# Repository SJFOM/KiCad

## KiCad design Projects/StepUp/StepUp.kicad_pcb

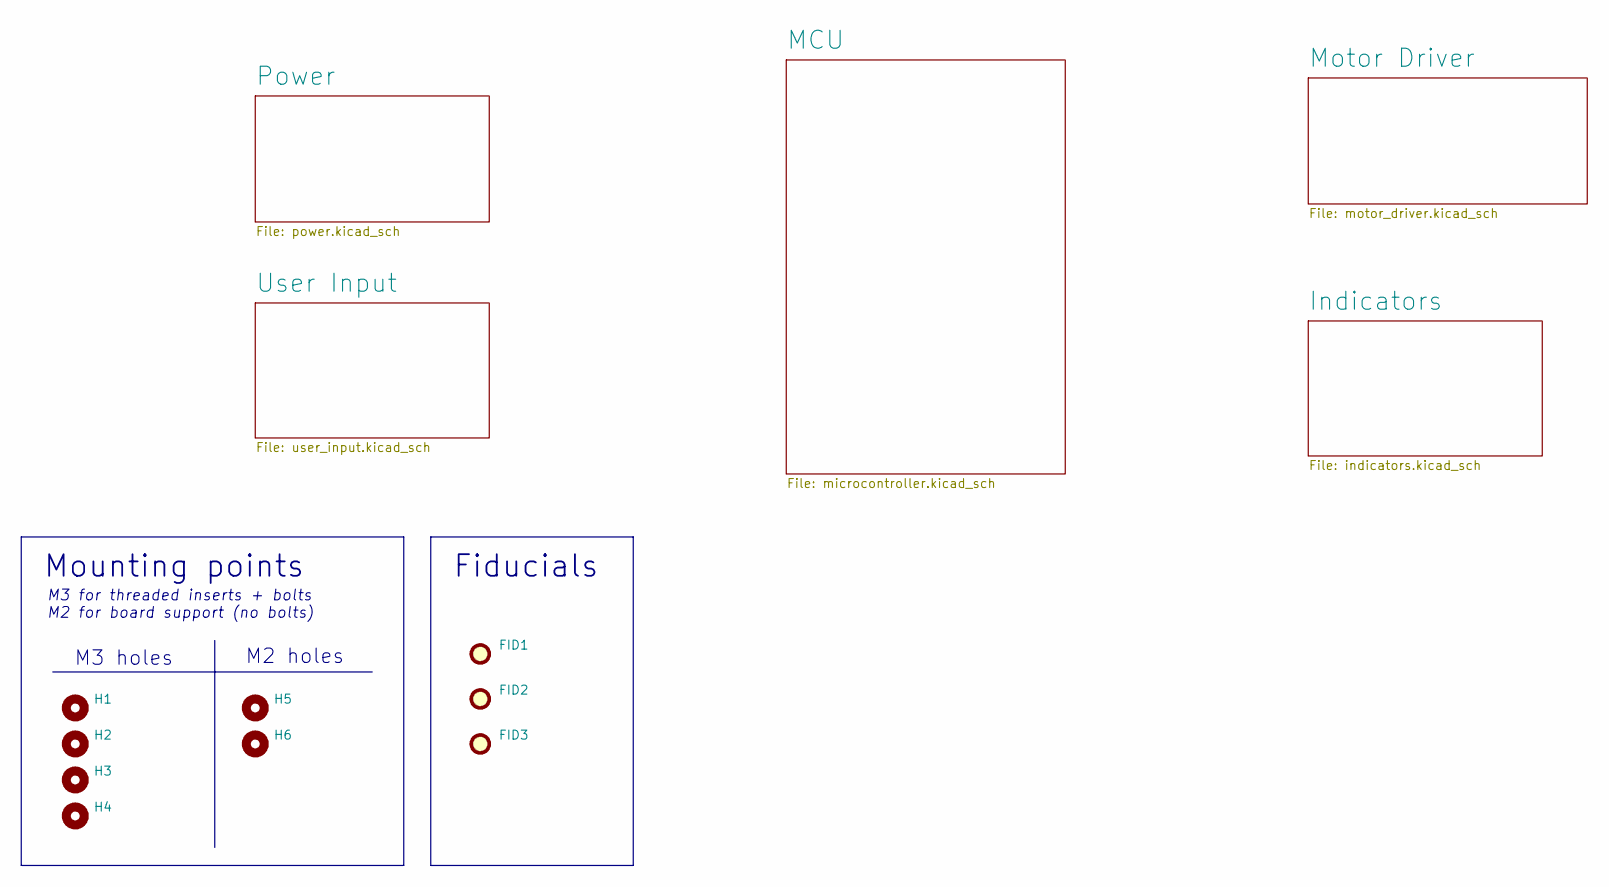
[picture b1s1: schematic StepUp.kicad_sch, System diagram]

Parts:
FID1, FID2, FID3: Fiducial; Fiducial_1mm_Mask2mm
H1, H2, H3, H4: MountingHole; MountingHole_3.2mm_M3_DIN965
H5, H6: MountingHole; MountingHole_2.2mm_M2

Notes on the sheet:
Mounting points
M3 holes
M2 holes
Fiducials
M3 for threaded inserts + bolts M2 for board support (no bolts)

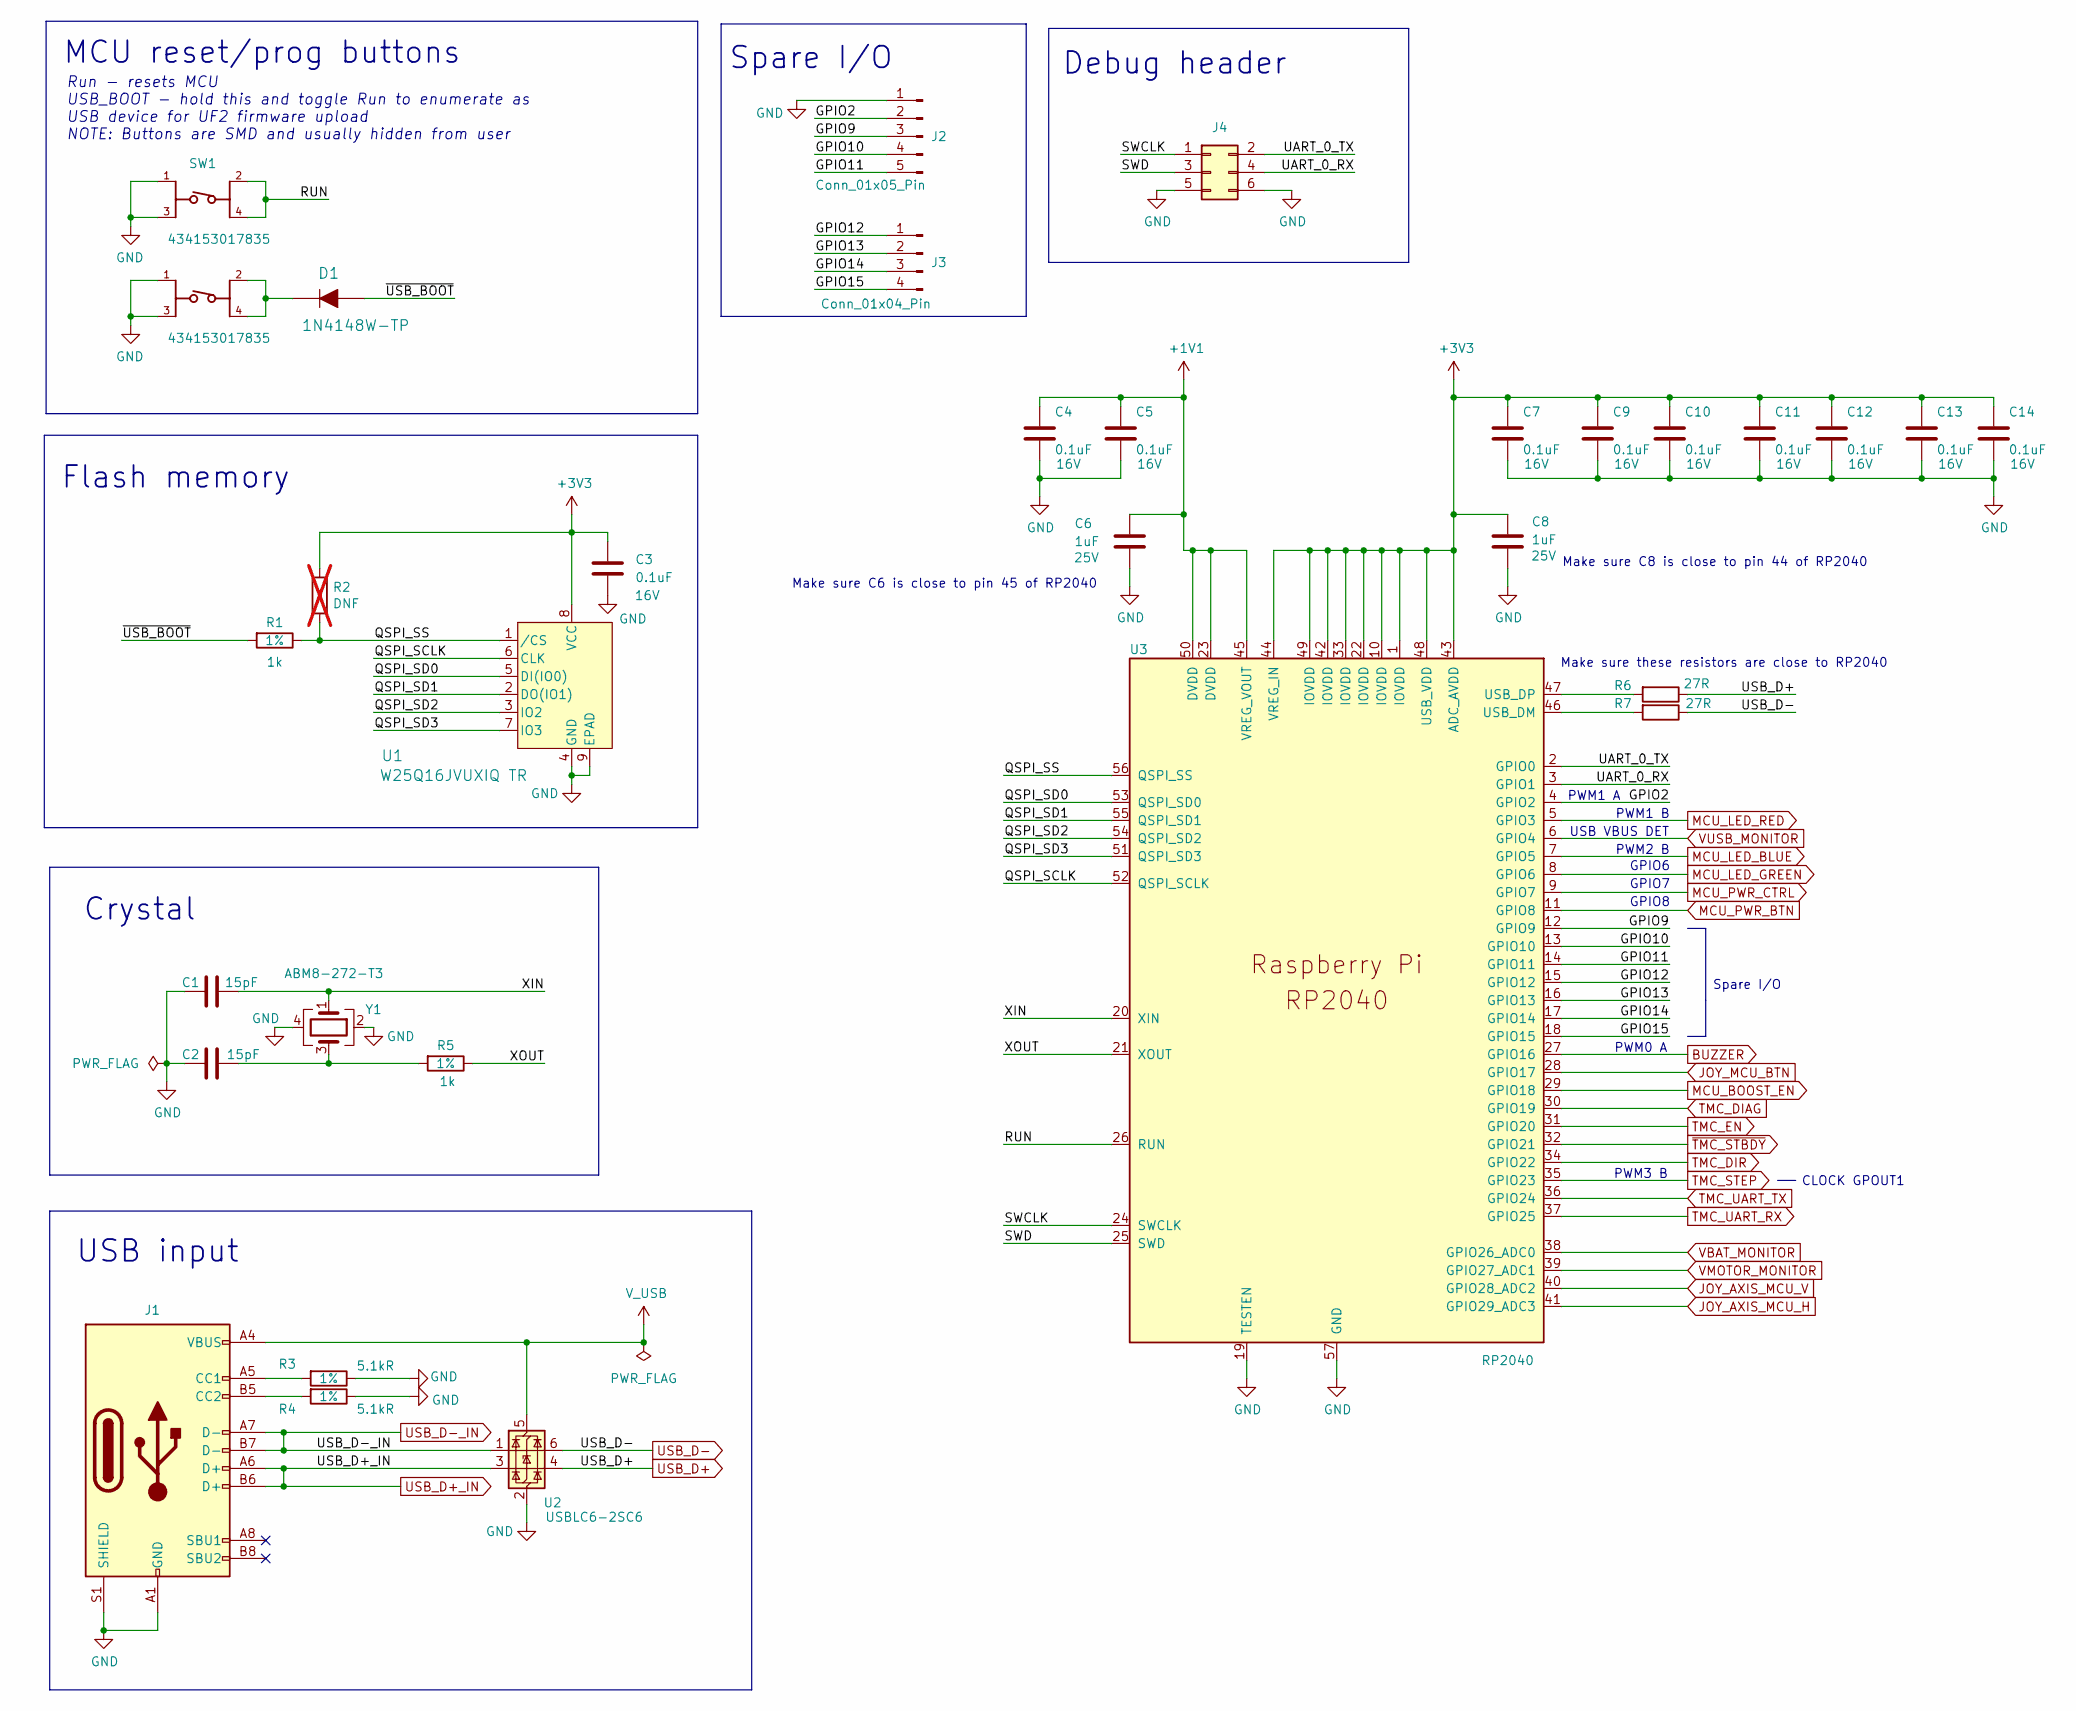
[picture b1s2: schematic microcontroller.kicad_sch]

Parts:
C1, C2: 15pF; C_0402_1005Metric; Tolerance 1%; Voltage 50V; MPN CC0402FRNPO9BN150
C3, C4, C5, C7, C9, C10, C11, C12, C13, C14: 0.1uF; C_0402_1005Metric; Voltage 16V; Tolerance 10%; MPN GRM155R61C104KA88D
C6, C8: 1uF; C_0603_1608Metric; Voltage 25V; Tolerance 10%; MPN GRM188R71E105KA12D
D1: 1N4148W-TP; SOD-123; MPN 1N4148W-TP; Digi-Key_PN 1N4148WTPMSCT-ND
J1: USB_C_Receptacle_USB2.0_16P; USB_C_Receptacle_GCT_USB4105-xx-A_16P_TopMnt_Horizontal; MPN USB4105-GF-A
J2: Conn_01x05_Pin; PinHeader_1x05_P2.54mm_Vertical
J3: Conn_01x04_Pin; PinHeader_1x04_P2.54mm_Vertical
J4: Conn_02x03_Odd_Even; PinHeader_2x03_P2.54mm_Vertical
R1, R5: 1k; R_0402_1005Metric; Tolerance 1%; MPN RC0402FR-071KL
R2: DNF; R_0402_1005Metric; not fitted
R3, R4: 5.1kR; R_0603_1608Metric; Tolerance 1%; MPN RC0603FR-075K1L
R6, R7: 27R; R_0402_1005Metric; Tolerance 1%; MPN RC0402FR-0727RL
SW1, SW2: 434153017835; 434153017835_434153017835; Voltage 12VDC; PART-NUMBER 434153017835
U1: W25Q16JVUXIQ TR; USON-8_UX_2x3x0p6_WIN; MPN W25Q16JVUXIQ TR
U2: USBLC6-2SC6; SOT-23-6; MPN USBLC6-2SC6
U3: RP2040; RP2040-QFN-56; MPN RP2040
Y1: ABM8-272-T3; Crystal_SMD_3225-4Pin_3.2x2.5mm; MPN ABM8-272-T3

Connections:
+1V1: C4.1, C5.1, C6.1, U3.23 (DVDD), U3.45 (VREG_VOUT), U3.50 (DVDD)
+3V3: C3.1, C7.1, C8.1, C9.1, C10.1, C11.1, C12.1, C13.1, C14.1, R2.1, U1.8 (VCC), U3.1 (IOVDD), U3.10 (IOVDD), U3.22 (IOVDD), U3.33 (IOVDD), U3.42 (IOVDD), U3.43 (ADC_AVDD), U3.44 (VREG_IN), U3.48 (USB_VDD), U3.49 (IOVDD); also elsewhere on the board
/MCU/GPIO2: J2.2, U3.4 (GPIO2)
/MCU/GPIO9: J2.3, U3.12 (GPIO9)
/MCU/GPIO10: J2.4, U3.13 (GPIO10)
/MCU/GPIO11: J2.5, U3.14 (GPIO11)
/MCU/GPIO12: J3.1, U3.15 (GPIO12)
/MCU/GPIO13: J3.2, U3.16 (GPIO13)
/MCU/GPIO14: J3.3, U3.17 (GPIO14)
/MCU/GPIO15: J3.4, U3.18 (GPIO15)
/MCU/QSPI_SCLK: U1.6 (CLK), U3.52 (QSPI_SCLK)
/MCU/QSPI_SD0: U1.5 (DI(IO0)), U3.53 (QSPI_SD0)
/MCU/QSPI_SD1: U1.2 (DO(IO1)), U3.55 (QSPI_SD1)
/MCU/QSPI_SD2: U1.3 (IO2), U3.54 (QSPI_SD2)
/MCU/QSPI_SD3: U1.7 (IO3), U3.51 (QSPI_SD3)
/MCU/QSPI_SS: R1.1, R2.2, U1.1 (/CS), U3.56 (QSPI_SS)
/MCU/RUN: SW1.2, SW1.4, U3.26 (RUN)
/MCU/SWCLK: J4.1, U3.24 (SWCLK)
/MCU/SWD: J4.3, U3.25 (SWD)
/MCU/UART_0_RX: J4.4, U3.3 (GPIO1)
/MCU/UART_0_TX: J4.2, U3.2 (GPIO0)
/MCU/XIN: C1.1, U3.20 (XIN), Y1.1
/MCU/XOUT: R5.1, U3.21 (XOUT)
/MCU/~USB_BOOT: D1.A, R1.2
BUZZER: U3.27 (GPIO16); also elsewhere on the board
GND: C1.2, C2.2, C3.2, C4.2, C5.2, C6.2, C7.2, C8.2, C9.2, C10.2, C11.2, C12.2, C13.2, C14.2, J1.A1 (GND), J1.A12 (GND), J1.B1 (GND), J1.B12 (GND), J1.S1 (SHIELD), J2.1, J4.5, J4.6, R3.1, R4.1, SW1.1, SW1.3, SW2.1, SW2.3, U1.4 (GND), U1.9 (EPAD), U2.2 (GND), U3.19 (TESTEN), U3.57 (GND), Y1.2, Y1.4; also elsewhere on the board
JOY_AXIS_MCU_H: U3.41 (GPIO29_ADC3); also elsewhere on the board
JOY_AXIS_MCU_V: U3.40 (GPIO28_ADC2); also elsewhere on the board
JOY_MCU_BTN: U3.28 (GPIO17); also elsewhere on the board
MCU_BOOST_EN: U3.29 (GPIO18); also elsewhere on the board
MCU_LED_BLUE: U3.7 (GPIO5); also elsewhere on the board
MCU_LED_GREEN: U3.8 (GPIO6); also elsewhere on the board
MCU_LED_RED: U3.5 (GPIO3); also elsewhere on the board
MCU_PWR_BTN: U3.11 (GPIO8); also elsewhere on the board
MCU_PWR_CTRL: U3.9 (GPIO7); also elsewhere on the board
unnamed: C2.1, R5.2, Y1.3
unnamed: D1.K, SW2.2, SW2.4
unnamed: J1.A5 (CC1), R3.2
unnamed: J1.B5 (CC2), R4.2
unnamed: R7.2, U3.46 (USB_DM)
unnamed: R6.2, U3.47 (USB_DP)
TMC_DIAG: U3.30 (GPIO19); also elsewhere on the board
TMC_DIR: U3.34 (GPIO22); also elsewhere on the board
TMC_EN: U3.31 (GPIO20); also elsewhere on the board
TMC_STEP: U3.35 (GPIO23); also elsewhere on the board
TMC_UART_RX: U3.37 (GPIO25); also elsewhere on the board
TMC_UART_TX: U3.36 (GPIO24); also elsewhere on the board
USB_D+: R6.1, U2.4 (I/O2)
USB_D+_IN: J1.A6 (D+), J1.B6 (D+), U2.3 (I/O2)
USB_D-: R7.1, U2.6 (I/O1)
USB_D-_IN: J1.A7 (D-), J1.B7 (D-), U2.1 (I/O1)
VBAT_MONITOR: U3.38 (GPIO26_ADC0); also elsewhere on the board
VMOTOR_MONITOR: U3.39 (GPIO27_ADC1); also elsewhere on the board
VUSB_MONITOR: U3.6 (GPIO4); also elsewhere on the board
V_USB: J1.A4 (VBUS), J1.A9 (VBUS), J1.B4 (VBUS), J1.B9 (VBUS), U2.5 (VBUS); also elsewhere on the board
~TMC_STBDY: U3.32 (GPIO21); also elsewhere on the board

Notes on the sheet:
CLOCK GPOUT1
GPIO6
Spare I/O
Make sure C8 is close to pin 44 of RP2040
Make sure C6 is close to pin 45 of RP2040
Debug header
PWM0 A
USB VBUS DET
MCU reset/prog buttons
Flash memory
PWM1 A
Crystal
PWM3 B
USB input
GPIO7
Run - resets MCU USB_BOOT - hold this and toggle Run to enumerate as USB device for UF2 firmware upload NOTE: Buttons are SMD and usually hidden from user
PWM2 B
PWM1 B
GPIO8
Make sure these resistors are close to RP2040

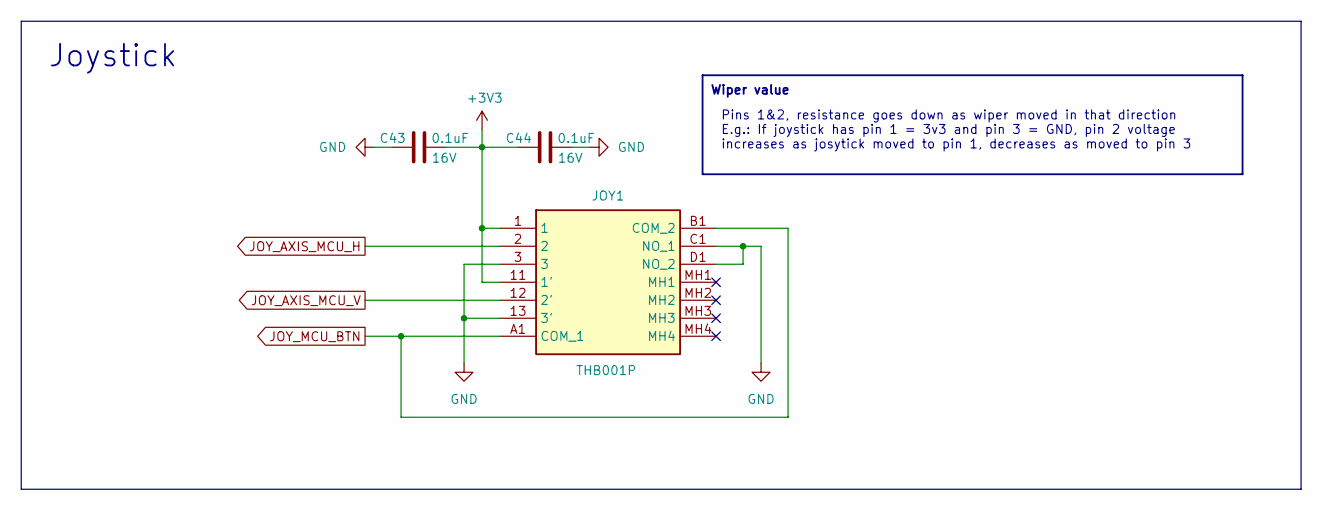
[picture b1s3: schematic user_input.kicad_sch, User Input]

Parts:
C43, C44: 0.1uF; C_0402_1005Metric; Voltage 16V; Tolerance 10%; MPN GRM155R61C104KA88D
JOY1: THB001P; Mouser Part Number 611-THB001P

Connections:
+3V3: C43.2, C44.1, JOY1.1, JOY1.11 (1'); also elsewhere on the board
GND: C43.1, C44.2, JOY1.3, JOY1.13 (3'), JOY1.C1 (NO_1), JOY1.D1 (NO_2); also elsewhere on the board
JOY_AXIS_MCU_H: JOY1.2; also elsewhere on the board
JOY_AXIS_MCU_V: JOY1.12 (2'); also elsewhere on the board
JOY_MCU_BTN: JOY1.A1 (COM_1), JOY1.B1 (COM_2); also elsewhere on the board

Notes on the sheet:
Wiper value
Pins 1&2, resistance goes down as wiper moved in that direction E.g.: If joystick has pin 1 = 3v3 and pin 3 = GND, pin 2 voltage increases as josytick moved to pin 1, decreases as moved to pin 3
Joystick

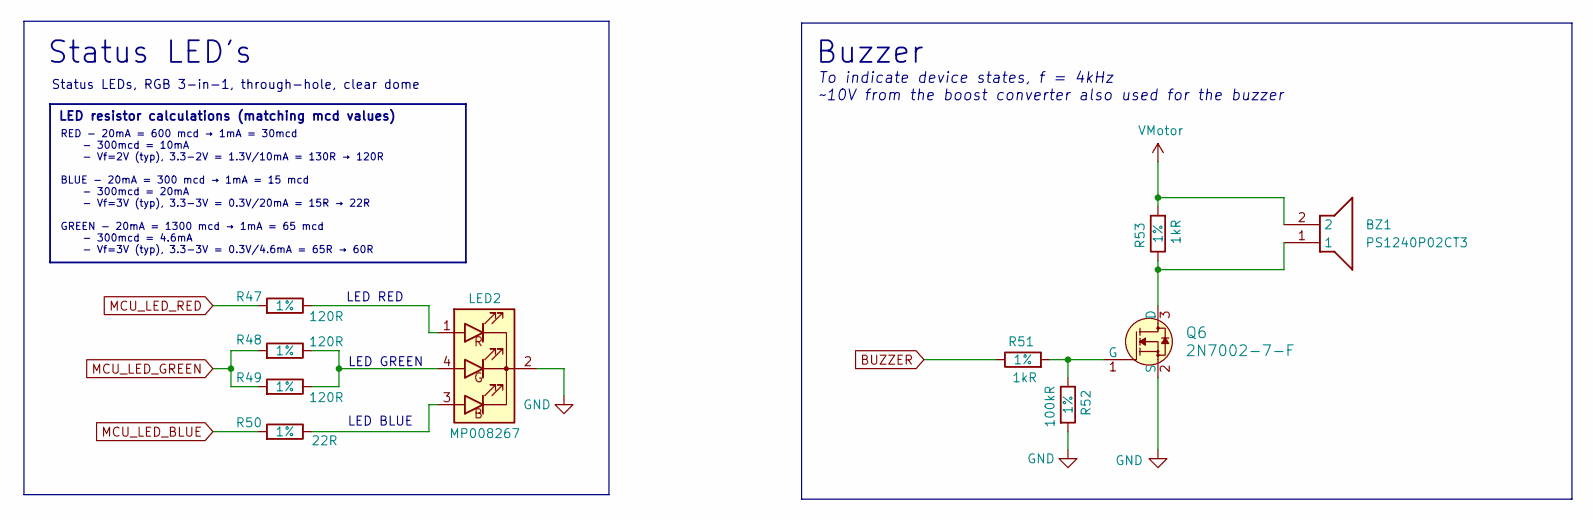
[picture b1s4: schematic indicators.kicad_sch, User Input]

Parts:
BZ1: PS1240P02CT3; PS1240P02BT; Mouser Part Number 810-PS1240P02CT3
LED2: MP008267; Manufacturer Part Number MP008267
Q6: 2N7002-7-F; SOT-23-3; MPN 2N7002-7-F; Digi-Key_PN 2N7002-FDICT-ND
R47, R48, R49: 120R; R_0603_1608Metric; Tolerance 1%; MPN RC0603FR-07120RL
R50: 22R; R_0603_1608Metric; Tolerance 1%; MPN RC0603FR-0722RL
R51, R53: 1kR; R_0603_1608Metric; Tolerance 1%; MPN RC0603FR-071KL
R52: 100kR; R_0603_1608Metric; Tolerance 1%; MPN RC0603FR-07100KL

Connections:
BUZZER: R51.1; also elsewhere on the board
GND: LED2.2, Q6.2 (S), R52.2; also elsewhere on the board
MCU_LED_BLUE: R50.2; also elsewhere on the board
MCU_LED_GREEN: R48.2, R49.2; also elsewhere on the board
MCU_LED_RED: R47.2; also elsewhere on the board
unnamed: LED2.1, R47.1
unnamed: LED2.3, R50.1
unnamed: LED2.4, R48.1, R49.1
unnamed: BZ1.1, Q6.3 (D), R53.1
unnamed: Q6.1 (G), R51.2, R52.1
VMotor: BZ1.2, R53.2; also elsewhere on the board

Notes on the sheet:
LED GREEN
LED RED
Status LED's
LED resistor calculations (matching mcd values)
Status LEDs, RGB 3-in-1, through-hole, clear dome
Buzzer
To indicate device states, f = 4kHz ~10V from the boost converter also used for the buzzer
RED - 20mA = 600 mcd → 1mA = 30mcd - 300mcd = 10mA - Vf=2V (typ), 3.3-2V = 1.3V/10mA = 130R → 120R BLUE - 20mA = 300 mcd → 1mA = 15 mcd - 300mcd = 20mA - Vf=3V (typ), 3.3-3V = 0.3V/20mA = 15R → 22R GREEN - 20mA = 1300 mcd → 1mA = 65 mcd - 300mcd = 4.6mA - Vf=3V (typ), 3.3-3V = 0.3V/4.6mA = 65R → 60R
LED BLUE

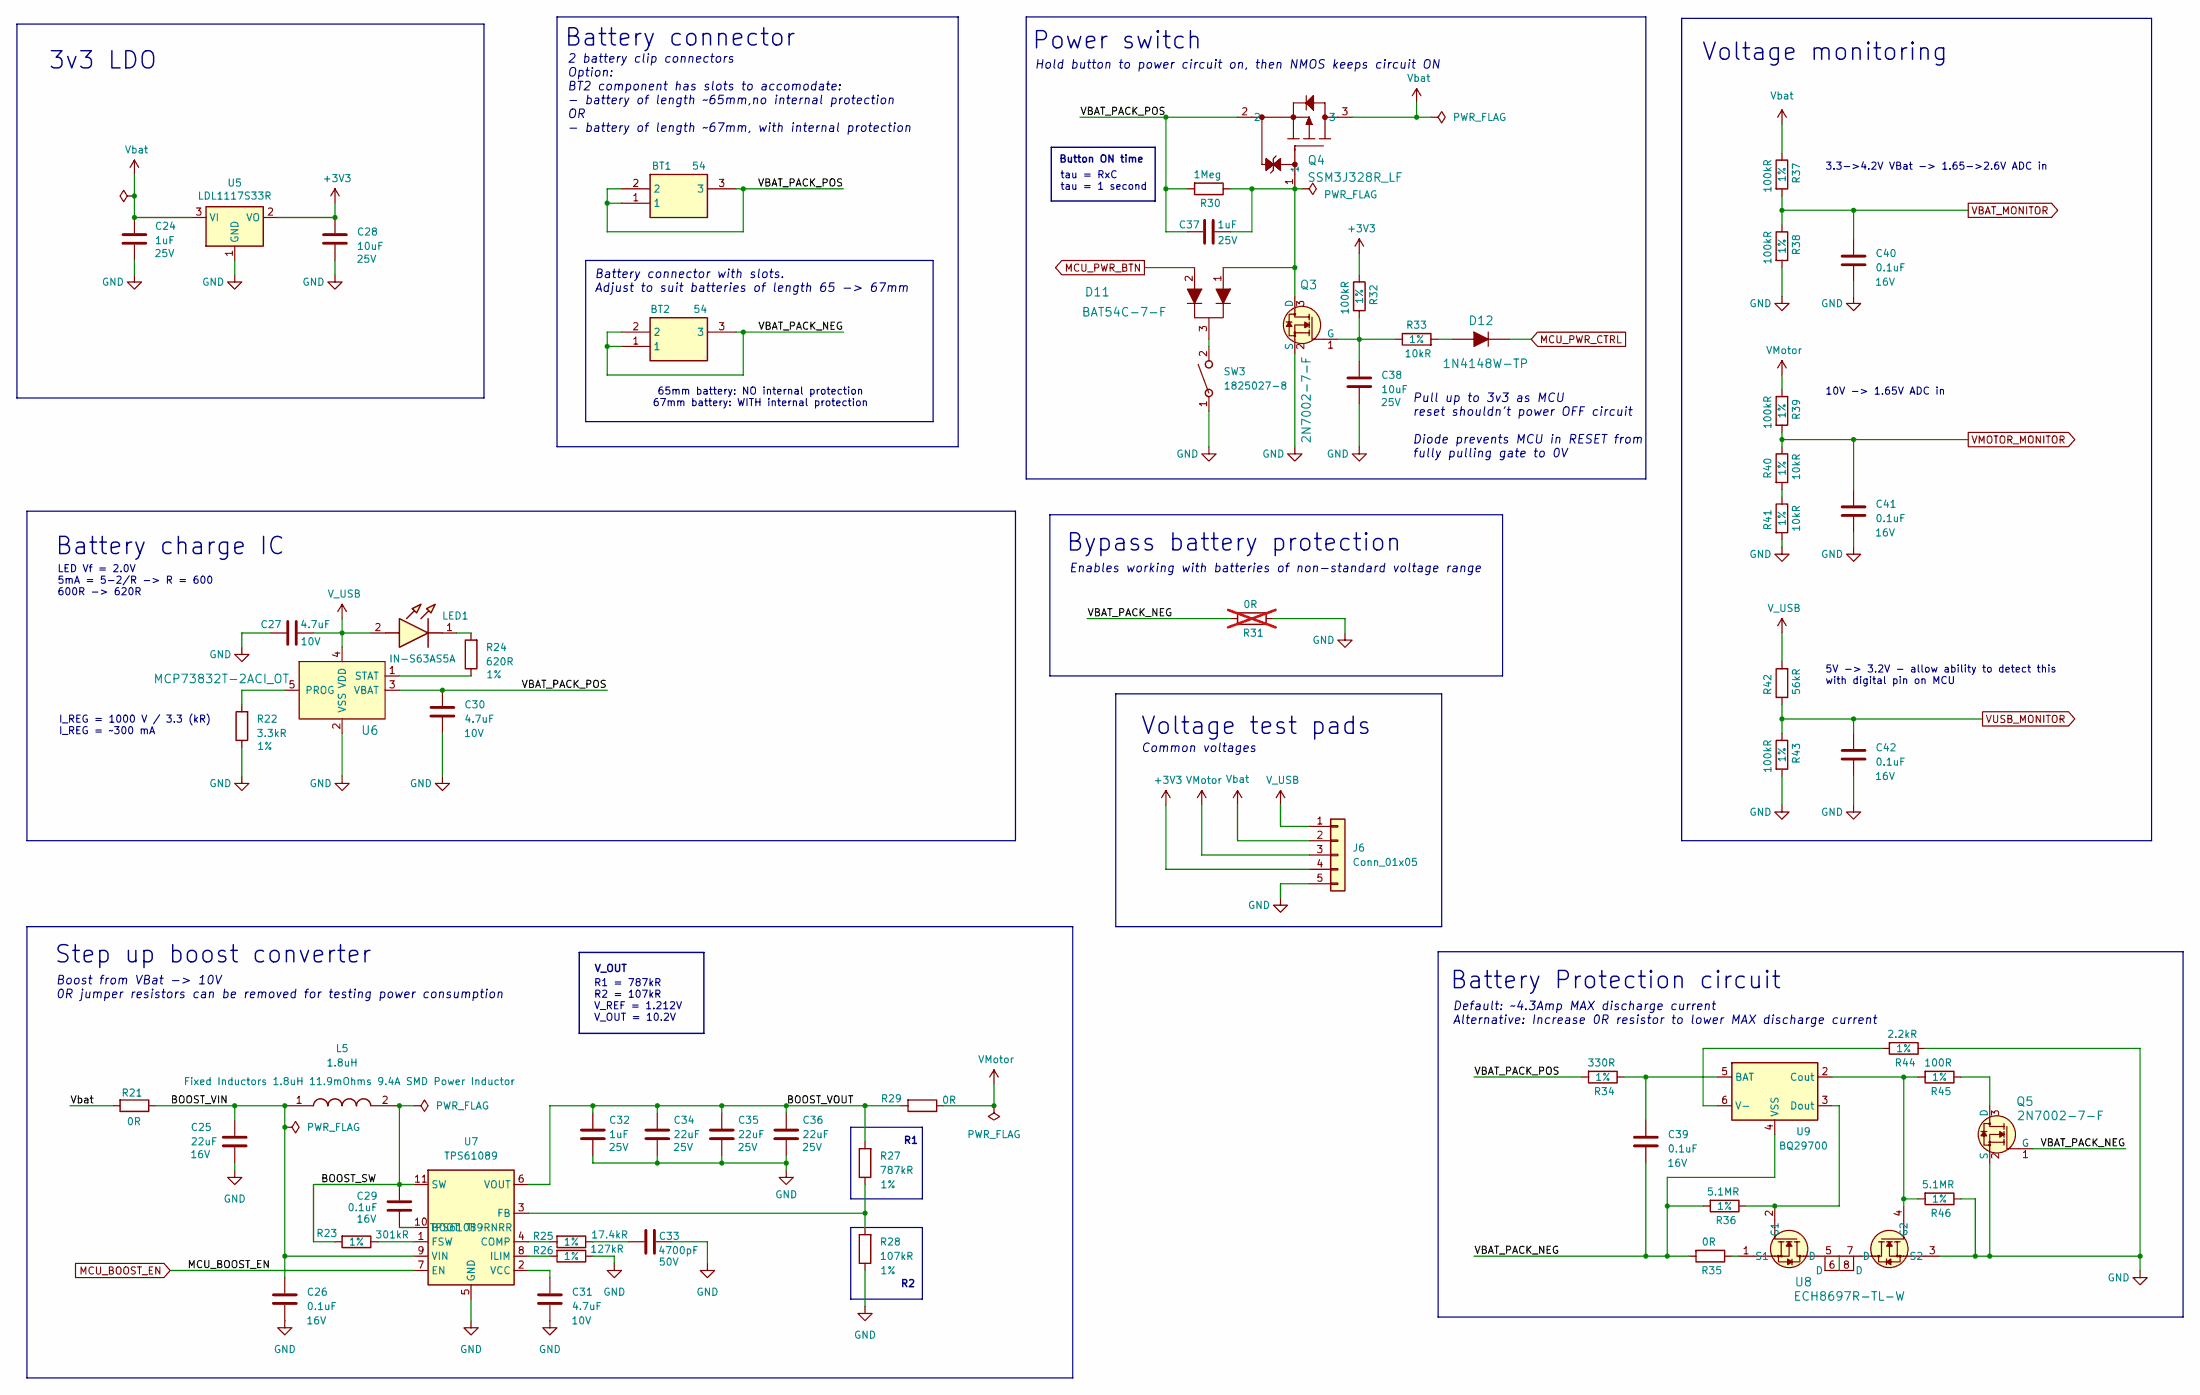
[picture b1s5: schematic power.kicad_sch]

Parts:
BT1: 54; Mouser Part Number 534-54
BT2: 54; 54_SLOT; Mouser Part Number 534-54
C24, C32, C37: 1uF; C_0603_1608Metric; Voltage 25V; Tolerance 10%; MPN GRM188R71E105KA12D
C25: 22uF; C_1206_3216Metric; Voltage 16V; Tolerance 10%; MPN GRM319R61C226KE15D
C26, C29, C39, C40, C41, C42: 0.1uF; C_0402_1005Metric; Voltage 16V; Tolerance 10%; MPN GRM155R61C104KA88D
C27, C30, C31: 4.7uF; C_0603_1608Metric; Voltage 10V; Tolerance 10%; MPN 0603ZD475KAT2A
C28, C38: 10uF; C_0603_1608Metric; Voltage 25V; Tolerance 10%; MPN GRM188R61E106KA73D
C33: 4700pF; C_0402_1005Metric; Voltage 50V; Tolerance 10%; MPN GRM155R61H472KA01D
C34, C35, C36: 22uF; C_1210_3225Metric; Voltage 25V; Tolerance 10%; MPN GRM32ER71E226KE15L
D11: BAT54C-7-F; SOT-23-3; MPN BAT54C-7-F; Digi-Key_PN BAT54C-FDICT-ND
D12: 1N4148W-TP; SOD-123; MPN 1N4148W-TP; Digi-Key_PN 1N4148WTPMSCT-ND
J6: Conn_01x05; PinHeader_1x05_P2.54mm_Vertical
L5: 1.8uH; INDPM9585X300N; MPN CDMC8D28NP-1R8MC; Mouser Part Number 851-CDMC8D28NP-1R8MC
LED1: IN-S63AS5A; INS63AS5UW; MPN IN-S63AS5A
Q3, Q5: 2N7002-7-F; SOT-23-3; MPN 2N7002-7-F; Digi-Key_PN 2N7002-FDICT-ND
Q4: SSM3J328R_LF; SOT-23F_TOS; MPN SSM3J328R,LF
R21, R29, R35: 0R; R_0603_1608Metric; MPN RC0603FR-070RL
R22: 3.3kR; R_0603_1608Metric; Tolerance 1%; MPN ERJU03F3301V
R23: 301kR; R_0402_1005Metric; Tolerance 1%; MPN CRCW0402301KFKED
R24: 620R; R_0603_1608Metric; Tolerance 1%; MPN RC0603FR-07620RL
R25: 17.4kR; R_0402_1005Metric; Tolerance 1%; MPN CRCW040217K4FKED
R26: 127kR; R_0402_1005Metric; Tolerance 1%; MPN CRCW0402127KFKED
R27: 787kR; R_0402_1005Metric; Tolerance 1%; MPN CRCW0402787KFKED
R28: 107kR; R_0402_1005Metric; Tolerance 1%; MPN CRCW0402107KFKED
R30: 1Meg; R_0603_1608Metric; Tolerance 1%; MPN RC0603FR-071ML
R31: 0R; R_0603_1608Metric; MPN RC0603FR-070RL; not fitted
R32, R37, R38, R39, R43: 100kR; R_0603_1608Metric; Tolerance 1%; MPN RC0603FR-07100KL
R33, R40, R41: 10kR; R_0603_1608Metric; Tolerance 1%; MPN RC0603FR-0710KL
R34: 330R; R_0603_1608Metric; Tolerance 1%; MPN RC0603FR-07330RL
R36, R46: 5.1MR; R_0603_1608Metric; Tolerance 1%; MPN RC0603FR-075M1L
R42: 56kR; R_0603_1608Metric; Tolerance 1%; MPN RC0603FR-0756KL
R44: 2.2kR; R_0402_1005Metric; Tolerance 1%; MPN RC0402FR-072K2L
R45: 100R; R_0603_1608Metric; Tolerance 1%; MPN RC0603FR-07100RL
SW3: 1825027-8; Manufacturer_Part_Number 1825027-8; Mouser Part Number 506-1825027-8
U5: LDL1117S33R; SOT-223-3_TabPin2; MPN LDL1117S33R
U6: MCP73832T-2ACI_OT; SOT-753; MPN MCP73832T-2ACI/OT; Digi-Key_PN MCP73832T-2ACI/OTCT-ND
U7: TPS61089; Texas_VQFN-RNR0011A-11; MPN TPS61089RNRR
U8: ECH8697R-TL-W; SOT-28FL-8_2P9X2P3_ONS; MPN ECH8697R-TL-W
U9: BQ29700; WSON-6_1.5x1.5mm_P0.5mm; MPN BQ29700DSER

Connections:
+3V3: C28.1, J6.4, R32.1, U5.2 (VO); also elsewhere on the board
/Power/BOOST_SW: C29.2, L5.2, R23.2, U7.11 (SW)
/Power/BOOST_VIN: C25.1, C26.1, L5.1, R21.1, U7.9 (VIN)
/Power/BOOST_VOUT: C32.1, C34.1, C35.1, C36.1, R27.2, R29.2, U7.6 (VOUT)
/Power/VBAT_PACK_NEG: BT2.1, BT2.2, BT2.3, C39.2, Q5.1 (G), R31.2, R35.2, R36.2, U9.4 (VSS)
/Power/VBAT_PACK_POS: BT1.1, BT1.2, BT1.3, C30.1, C37.1, Q4.2, R30.2, R34.2, U6.3 (VBAT)
GND: C24.2, C25.2, C26.2, C27.1, C28.2, C30.2, C31.2, C32.2, C33.2, C34.2, C35.2, C36.2, C38.2, C40.2, C41.2, C42.2, J6.5, Q3.2 (S), Q5.2 (S), R22.1, R26.1, R28.1, R31.1, R38.2, R41.2, R43.2, R44.1, R46.1, SW3.1, U5.1 (GND), U6.2 (VSS), U7.5 (GND), U8.3 (S2); also elsewhere on the board
MCU_BOOST_EN: U7.7 (EN); also elsewhere on the board
MCU_PWR_BTN: D11.2; also elsewhere on the board
MCU_PWR_CTRL: D12.K; also elsewhere on the board
unnamed: C33.1, R25.1
unnamed: D11.3, SW3.2
unnamed: D12.A, R33.2
unnamed: LED1.1 (K), R24.2
unnamed: C37.2, D11.1, Q3.3 (D), Q4.1, R30.1
unnamed: C38.1, Q3.1 (G), R32.2, R33.1
unnamed: Q5.3 (D), R45.1
unnamed: R40.2, R41.1
unnamed: R22.2, U6.5 (PROG)
unnamed: R24.1, U6.1 (STAT)
unnamed: C29.1, U7.10 (BOOT)
unnamed: R25.2, U7.4 (COMP)
unnamed: R27.1, R28.2, U7.3 (FB)
unnamed: R23.1, U7.1 (FSW)
unnamed: R26.2, U7.8 (ILIM)
unnamed: C31.1, U7.2 (VCC)
unnamed: U8.5 (D), U8.6 (D), U8.7 (D), U8.8 (D)
unnamed: R36.1, U8.2 (G1), U9.3 (Dout)
unnamed: R45.2, R46.2, U8.4 (G2), U9.2 (Cout)
unnamed: R35.1, U8.1 (S1)
unnamed: C39.1, R34.1, U9.5 (BAT)
unnamed: R44.2, U9.6 (V-)
VBAT_MONITOR: C40.1, R37.2, R38.1; also elsewhere on the board
VMOTOR_MONITOR: C41.1, R39.2, R40.1; also elsewhere on the board
VMotor: J6.3, R29.1, R39.1; also elsewhere on the board
VUSB_MONITOR: C42.1, R42.1, R43.1; also elsewhere on the board
V_USB: C27.2, J6.1, LED1.2 (A), R42.2, U6.4 (VDD); also elsewhere on the board
Vbat: C24.1, J6.2, Q4.3, R21.2, R37.1, U5.3 (VI)

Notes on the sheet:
Step up boost converter
3v3 LDO
Battery Protection circuit
V_OUT
LED Vf = 2.0V 5mA = 5-2/R -> R = 600 600R -> 620R
Enables working with batteries of non-standard voltage range
Hold button to power circuit on, then NMOS keeps circuit ON
Boost from VBat -> 10V 0R jumper resistors can be removed for testing power consumption
Default: ~4.3Amp MAX discharge current Alternative: Increase 0R resistor to lower MAX discharge current
Battery connector with slots. Adjust to suit batteries of length 65 -> 67mm
Power switch
65mm battery: NO internal protection 67mm battery: WITH internal protection
Bypass battery protection
Voltage test pads
Battery connector
Pull up to 3v3 as MCU reset shouldn't power OFF circuit Diode prevents MCU in RESET from fully pulling gate to 0V
Common voltages
R1 = 787kR R2 = 107kR V_REF = 1.212V V_OUT = 10.2V
10V -> 1.65V ADC in
Voltage monitoring
3.3->4.2V VBat -> 1.65->2.6V ADC in
5V -> 3.2V - allow ability to detect this with digital pin on MCU
tau = RxC tau = 1 second
Battery charge IC
Button ON time
2 battery clip connectors Option: BT2 component has slots to accomodate: - battery of length ~65mm,no internal protection OR - battery of length ~67mm, with internal protection
I_REG = 1000 V / 3.3 (kR) I_REG = ~300 mA

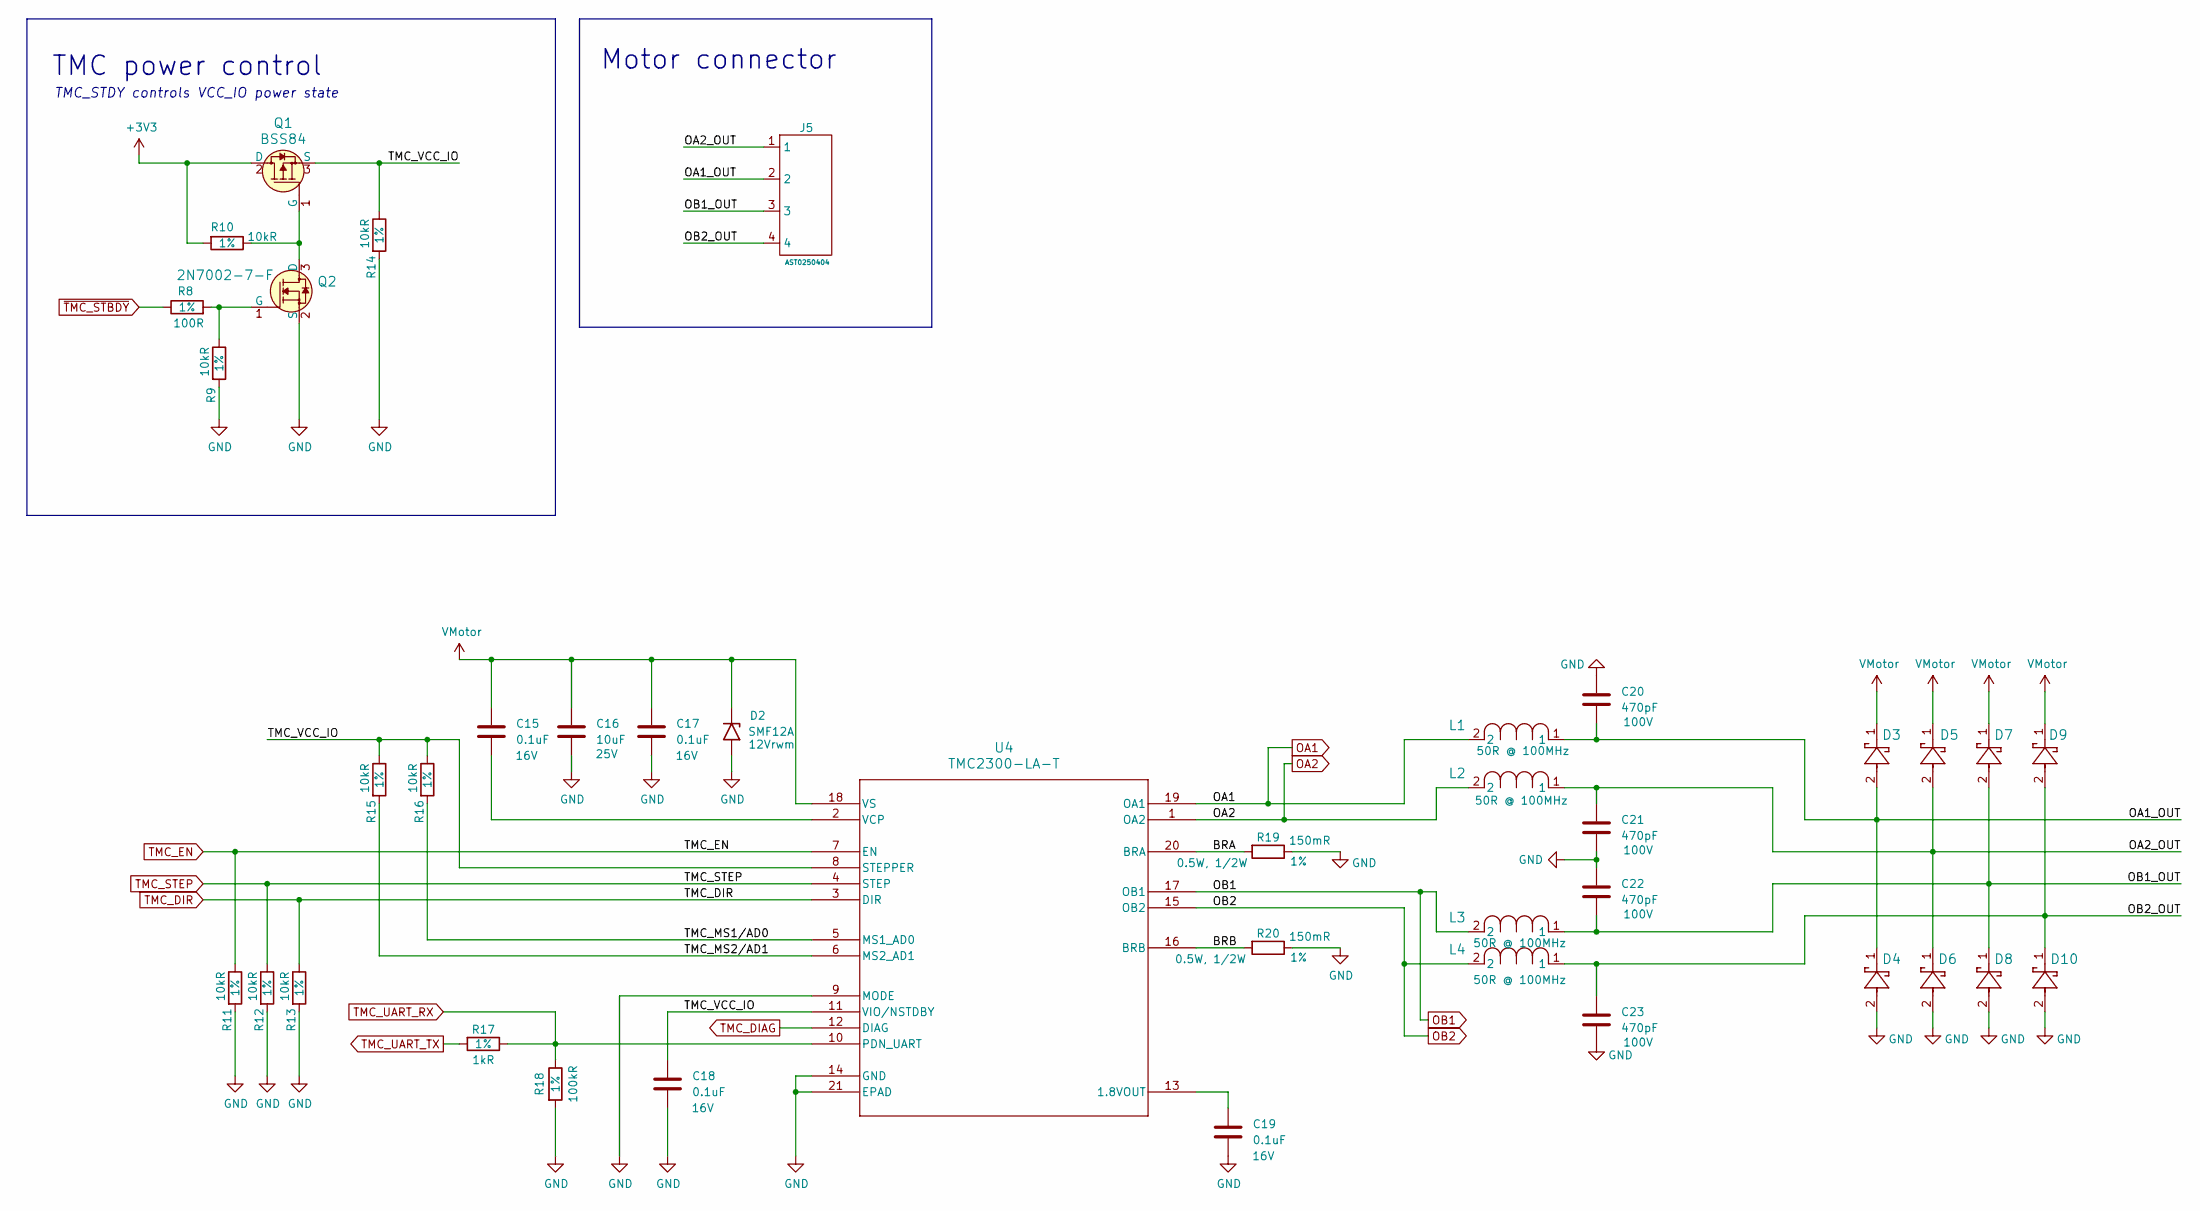
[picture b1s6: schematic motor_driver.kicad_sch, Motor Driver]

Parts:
C15, C17, C18, C19: 0.1uF; C_0402_1005Metric; Voltage 16V; Tolerance 10%; MPN GRM155R61C104KA88D
C16: 10uF; C_0603_1608Metric; Voltage 25V; Tolerance 10%; MPN GRM188R61E106KA73D
C20, C21, C22, C23: 470pF; C_0402_1005Metric; Voltage 100V; Tolerance 10%; MPN CC0402KRX7R0BB471
D2: SMF12A; D_SMF; MPN SMF12A-M3-08
D3, D4, D5, D6, D7, D8, D9, D10: B5819W-TP; SDO_SOD-123_MCC; MPN B5819W-TP
J5: AST0250404; AST250404; MPN AST0250404
L1, L2, L3, L4: HI1206T500R-10; IND_HI1206T500R-10_LRD; MPN HI1206T500R-10
Q1: BSS84; SOT-23-3; MPN BSS84; Digi-Key_PN BSS84CT-ND
Q2: 2N7002-7-F; SOT-23-3; MPN 2N7002-7-F; Digi-Key_PN 2N7002-FDICT-ND
R8: 100R; R_0603_1608Metric; Tolerance 1%; MPN RC0603FR-07100RL
R9, R10, R11, R12, R13, R14, R15, R16: 10kR; R_0603_1608Metric; Tolerance 1%; MPN RC0603FR-0710KL
R17: 1kR; R_0603_1608Metric; Tolerance 1%; MPN RC0603FR-071KL
R18: 100kR; R_0603_1608Metric; Tolerance 1%; MPN RC0603FR-07100KL
R19, R20: 150mR; R_1206_3216Metric; Tolerance 1%; MPN CRL1206-FW-R150ELF
U4: TMC2300-LA-T; QFN20_3x3_TRI-M; MPN TMC2300-LA-T

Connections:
+3V3: Q1.2 (D), R10.2; also elsewhere on the board
/Motor Driver/BRA: R19.2, U4.20 (BRA)
/Motor Driver/BRB: R20.2, U4.16 (BRB)
/Motor Driver/OA1_OUT: C20.2, D3.2, D4.1, J5.2, L1.1
/Motor Driver/OA2_OUT: C21.1, D5.2, D6.1, J5.1, L2.1
/Motor Driver/OB1_OUT: C22.2, D7.2, D8.1, J5.3, L3.1
/Motor Driver/OB2_OUT: C23.1, D9.2, D10.1, J5.4, L4.1
/Motor Driver/TMC_MS1/AD0: R16.2, U4.5 (MS1_AD0)
/Motor Driver/TMC_MS2/AD1: R15.2, U4.6 (MS2_AD1)
/Motor Driver/TMC_VCC_IO: C18.1, Q1.3 (S), R14.1, R15.1, R16.1, U4.8 (STEPPER), U4.11 (VIO/NSTDBY)
GND: C16.2, C17.2, C18.2, C19.2, C20.1, C21.2, C22.1, C23.2, D2.2 (A2), D4.2, D6.2, D8.2, D10.2, Q2.2 (S), R9.2, R11.2, R12.2, R13.2, R14.2, R18.2, R19.1, R20.1, U4.9 (MODE), U4.14 (GND), U4.21 (EPAD); also elsewhere on the board
unnamed: Q1.1 (G), Q2.3 (D), R10.1
unnamed: Q2.1 (G), R8.2, R9.1
unnamed: C19.1, U4.13 (1.8VOUT)
unnamed: C15.2, U4.2 (VCP)
OA1: L1.2, U4.19 (OA1)
OA2: L2.2, U4.1 (OA2)
OB1: L3.2, U4.17 (OB1)
OB2: L4.2, U4.15 (OB2)
TMC_DIAG: U4.12 (DIAG); also elsewhere on the board
TMC_DIR: R13.1, U4.3 (DIR); also elsewhere on the board
TMC_EN: R11.1, U4.7 (EN); also elsewhere on the board
TMC_STEP: R12.1, U4.4 (STEP); also elsewhere on the board
TMC_UART_RX: R17.1, R18.1, U4.10 (PDN_UART); also elsewhere on the board
TMC_UART_TX: R17.2; also elsewhere on the board
VMotor: C15.1, C16.1, C17.1, D2.1 (A1), D3.1, D5.1, D7.1, D9.1, U4.18 (VS); also elsewhere on the board
~TMC_STBDY: R8.1; also elsewhere on the board

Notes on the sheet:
TMC_STDY controls VCC_IO power state
TMC power control
Motor connector
